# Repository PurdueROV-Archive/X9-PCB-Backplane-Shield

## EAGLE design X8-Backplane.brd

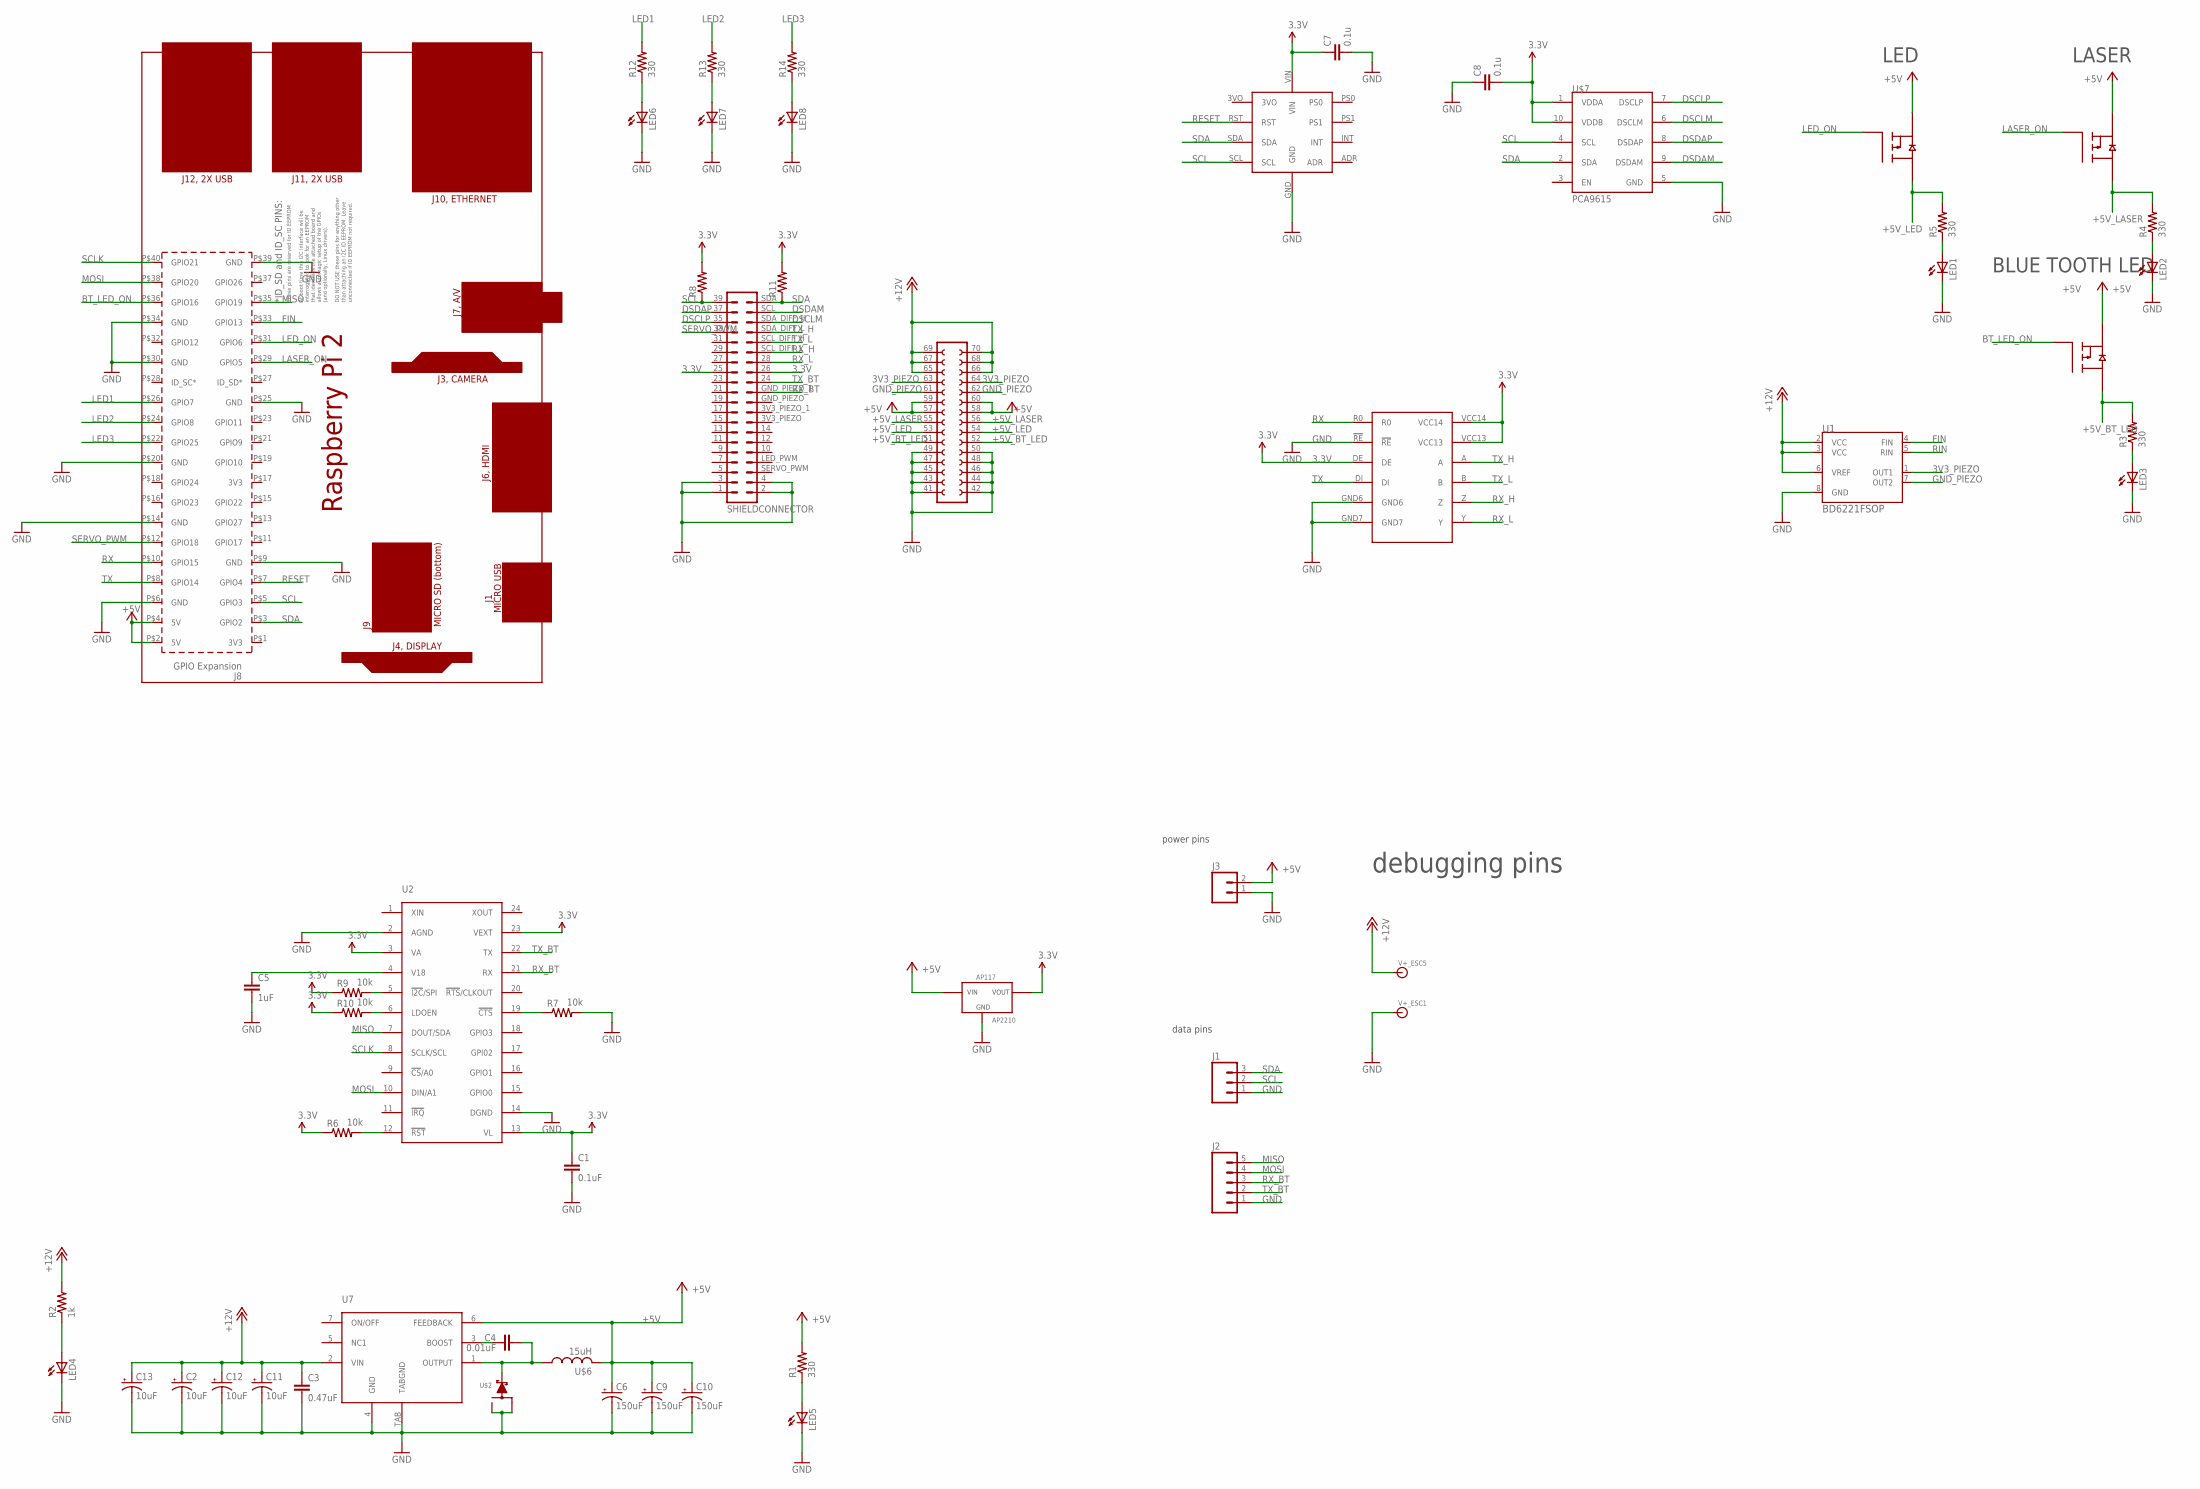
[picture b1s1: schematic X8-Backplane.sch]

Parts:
C1: 0.1uF; 0603-CAP
C2, C11, C12, C13: 10uF; CTAN(7.30_4.30MM)
C3: 0.47uF; 0603
C4: 0.01uF; 0603-CAP
C5: 1uF; 0603-CAP
C6, C9, C10: 150uF; CTAN(7.30_4.30MM)
C7, C8: 0.1u; 0603-CAP
J1: M03PTH; 1X03
J2: M05PTH; 1X05
J3: M02PTH; 1X02
LED1, LED2, LED3, LED4, LED5, LED6, LED7, LED8: LEDSML0603; SML0603
PCB1: RPI2
R1, R3, R4, R5, R12, R13, R14: 330; R0603
R2: 1k; R0603
R6, R7, R9, R10: 10k; 0603-RES
R8, R11: RESISTOR0603-RES; 0603-RES
U1: BD6221FSOP; SOP8
U2: MAX3107SSOP; SSOP-24
U4, U5, U6: FQB27P06; TO263-3
U7: LM2678
U$1: MAX3491
U$2: SWITCHMODE_SCHOTTKY; DPAK-3
U$3: BNO055_9DOF_BREAKOUT; BNO055
U$4: SHIELDCONNECTOR; 20X2PIN
U$5: AP2210; SOT-23-3
U$6: 15uH; HCMA1305
U$7: PCA9615; MSOP_10
V+_ESC1, V+_ESC5: BANANA_CONN

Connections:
3.3V: C1.1, C7.1, C8.2, R6.1, R8.2, R9.1, R10.1, R11.2, U2.3 (VA), U2.13 (VL), U2.23 (VEXT), U$1.DE, U$1.VCC13, U$1.VCC14, U$3.VIN, U$4.25, U$4.26, U$5.VOUT, U$7.1 (VDDA), U$7.10 (VDDB)
3V3_PIEZO: U1.1 (OUT1), U$4.63 (23), U$4.64 (24)
+5V: C6.+, C9.+, C10.+, J3.2, PCB1.P$2 (5V), PCB1.P$4 (5V), R1.2, U4.3 (S2), U5.3 (S2), U6.3 (S2), U7.6 (FEEDBACK), U$4.57 (17), U$4.58 (18), U$4.59 (19), U$4.60 (20), U$5.VIN, U$6.P$2 (2)
+5V_BT_LED: R3.2, U6.TAB (D2), U$4.51 (11), U$4.52 (12)
+5V_LASER: R4.2, U5.TAB (D2), U$4.55 (15), U$4.56 (16)
+5V_LED: R5.2, U4.TAB (D2), U$4.53 (13), U$4.54 (14)
+12V: C2.+, C3.1, C11.+, C12.+, C13.+, R2.2, U1.2 (VCC), U1.3 (VCC), U1.6 (VREF), U7.2 (VIN), U$4.65 (25), U$4.66 (26), U$4.67 (27), U$4.68 (28), U$4.69 (12V), U$4.70 (30), V+_ESC5.P$1
BT_LED_ON: PCB1.P$36 (GPIO16), U6.1 (G2)
DSCLM: U$4.SDA_DIFF_H, U$7.6 (DSCLM)
DSCLP: U$4.35, U$7.7 (DSCLP)
DSDAM: U$4.SCL, U$7.9 (DSDAM)
DSDAP: U$4.37, U$7.8 (DSDAP)
FIN: PCB1.P$33 (GPIO13), U1.4 (FIN)
GND: C1.2, C2.-, C3.2, C5.2, C6.-, C7.2, C8.1, C9.-, C10.-, C11.-, C12.-, C13.-, J1.1, J2.1, J3.1, LED1.C, LED2.C, LED3.C, LED4.C, LED5.C, LED6.C, LED7.C, LED8.C, PCB1.P$6 (GND), PCB1.P$9 (GND), PCB1.P$14 (GND), PCB1.P$20 (GND), PCB1.P$25 (GND), PCB1.P$30 (GND), PCB1.P$34 (GND), PCB1.P$39 (GND), R7.2, U1.8 (GND), U2.2 (AGND), U2.14 (DGND), U7.4 (GND), U7.TAB (TABGND), U$1.!RE, U$1.GND6, U$1.GND7, U$2.P$1, U$2.P$3, U$3.GND, U$4.1, U$4.2, U$4.3, U$4.4, U$4.41 (1), U$4.42 (2), U$4.43 (3), U$4.44 (4), U$4.45 (5), U$4.46 (6), U$4.47 (7), U$4.48 (8), U$4.49 (9), U$4.50 (10), U$5.GND, U$7.5 (GND), V+_ESC1.P$1
GND_PIEZO: U1.7 (OUT2), U$4.61 (21), U$4.62 (22)
LASER_ON: PCB1.P$29 (GPIO5), U5.1 (G2)
LED1: PCB1.P$26 (GPIO7), R12.2
LED2: PCB1.P$24 (GPIO8), R13.2
LED3: PCB1.P$22 (GPIO25), R14.2
LED_ON: PCB1.P$31 (GPIO6), U4.1 (G2)
MISO: J2.5, PCB1.P$35 (GPIO19), U2.7 (DOUT/SDA)
MOSI: J2.4, PCB1.P$38 (GPIO20), U2.10 (DIN/A1)
unnamed: LED5.A, R1.1
unnamed: LED4.A, R2.1
unnamed: LED1.A, R5.1
unnamed: LED2.A, R4.1
unnamed: LED3.A, R3.1
unnamed: R6.2, U2.12 (!RST!)
unnamed: R7.1, U2.19 (!CTS!)
unnamed: C5.1, U2.4 (V18)
unnamed: R9.2, U2.5 (!I2C!/SPI)
unnamed: R10.2, U2.6 (LDOEN)
unnamed: LED6.A, R12.1
unnamed: LED7.A, R13.1
unnamed: LED8.A, R14.1
unnamed: C4.1, U7.3 (BOOST)
unnamed: C4.2, U7.1 (OUTPUT), U$2.P$4, U$6.P$1 (1)
RESET: PCB1.P$7 (GPIO4), U$3.RST
RIN: U1.5 (RIN)
RX: PCB1.P$10 (GPIO15), U$1.R0
RX_BT: J2.3, U2.21 (RX), U$4.GND_PIEZO_1
RX_H: U$1.Z, U$4.SCL_DIFF_L
RX_L: U$1.Y, U$4.28
SCL: J1.2, PCB1.P$5 (GPIO3), R8.1, U$3.SCL, U$4.39, U$7.4 (SCL)
SCLK: PCB1.P$40 (GPIO21), U2.8 (SCLK/SCL)
SDA: J1.3, PCB1.P$3 (GPIO2), R11.1, U$3.SDA, U$4.SDA, U$7.2 (SDA)
SERVO_PWM: PCB1.P$12 (GPIO18), U$4.33
TX: PCB1.P$8 (GPIO14), U$1.DI
TX_BT: J2.2, U2.22 (TX), U$4.24
TX_H: U$1.A, U$4.SDA_DIFF_L
TX_L: U$1.B, U$4.SCL_DIFF_H

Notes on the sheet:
LED
LASER
BLUE TOOTH LED
debugging pins
power pins
data pins

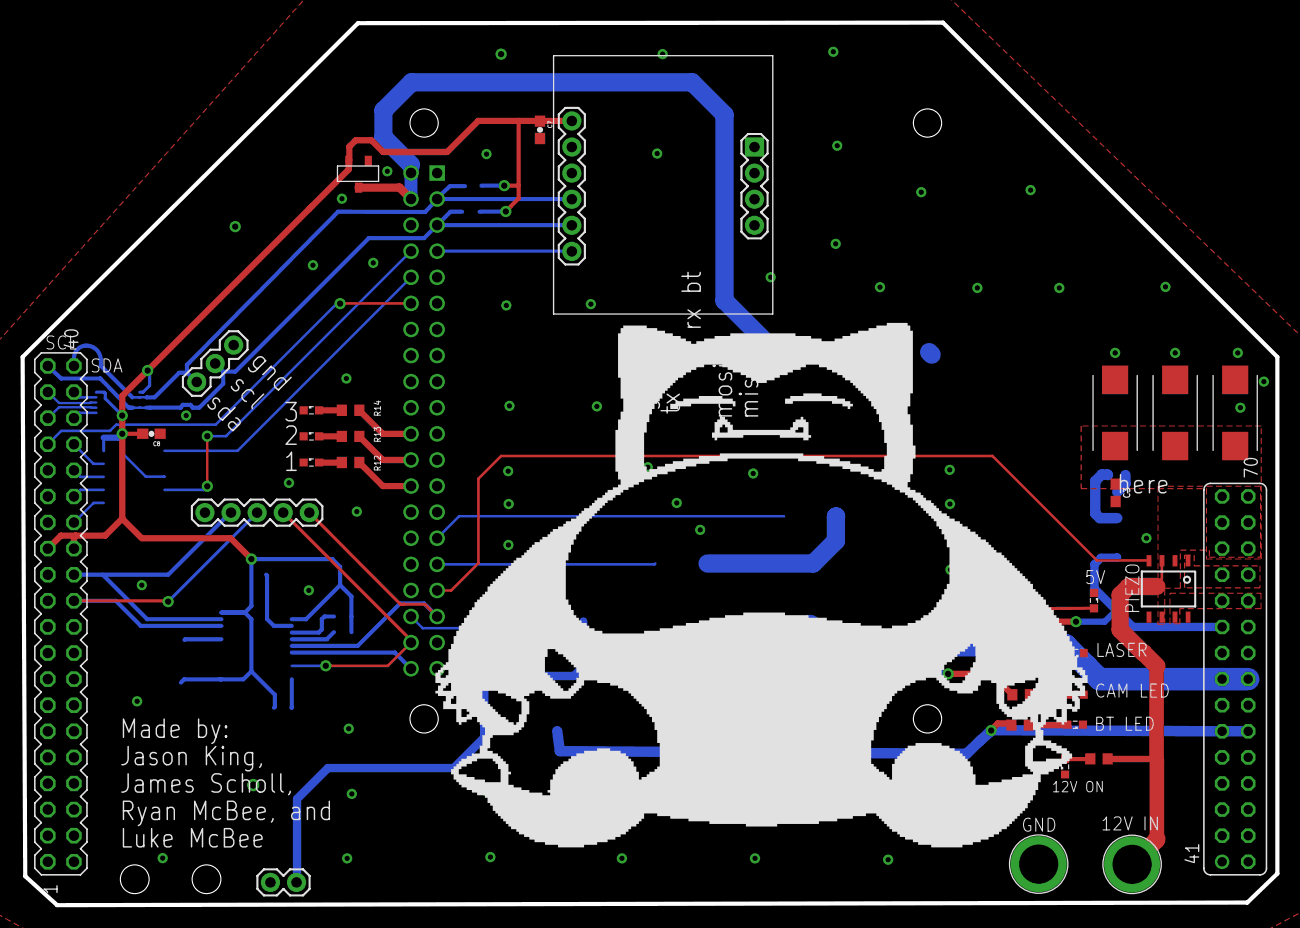
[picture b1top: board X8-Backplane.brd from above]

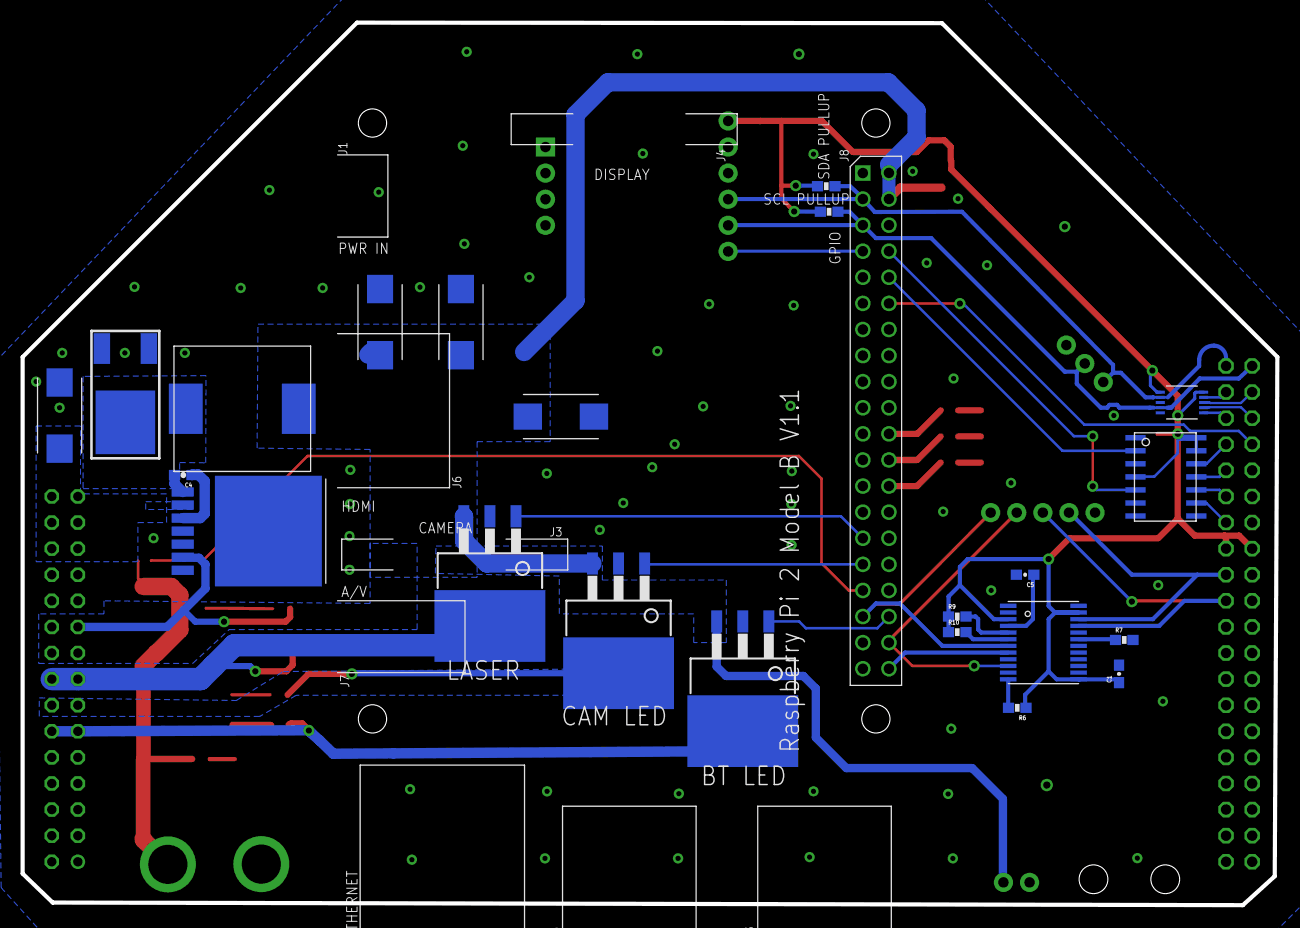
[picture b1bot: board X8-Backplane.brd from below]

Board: 2 copper layers, 122.1 x 85.9 mm, 54 parts (23 on the bottom side), 50 nets.

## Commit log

2016-11-02 OutputJob
2016-11-02 Added part for raspberry pi, 5V -> 3.3V buck converter, and IMU pins
2016-11-03 changed outside perimeter
2016-11-03 small modification to outline
2016-11-05 Intermediate layout
2016-11-05 Finished preliminary layout - probably needs revision
2016-11-06 added brd to brd connector
2016-11-12 because I can
2016-11-16 Mostly routed
2016-11-24 removed buck regulator circuit
2016-11-24 added some new parts
2016-11-24 finished adding components, added descriptions of pins
2016-11-25 first draft of the sechematic. Almost there!
2016-11-25 Added a mosfet for an led for the blue tooth
2016-11-27 Started initial routing on the board
2016-11-27 Leaving the rest to Ryan, not sure I can work with the layout given to me
2016-11-30 Redid routing and moved components
2016-11-30 Moved some more components and added vias to reconnect isolated grounds
2016-12-04 Almost done with routing - stil have to add vias and extra debugging pinouts
2016-12-04 Finished routing except for any debug pins and possible extra vias
2016-12-04 minor changes by Ryan
2016-12-04 made the bottom flat
2016-12-04 added buck regulator
2016-12-04 added more gnd vias
2016-12-07 Moved the buck regulator parts
2016-12-07 To be reviewed
2016-12-07 minor tweaks
2016-12-10 modified wiring of buck regulator
2016-12-10 added LEDs
2016-12-10 added SPI to UART ship
2016-12-11 Wired the spi to serial circuit
2016-12-15 almost done reviewing the board
2016-12-18 add holes for possible usb hub mount
2016-12-19 added two gnd vias
2016-12-21 Fixed routing issues
2016-12-23 modified the silkscreen
2016-12-23 added names
2016-12-24 minor changes to i2c lines
2016-12-26 cleaned up gnd plane and added labels
2016-12-28 added snorlax!
2016-12-29 minor changes
2016-12-30 Edited the silkscreen

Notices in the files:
parts and their libraries:
SparkFun-Passives: Licensing: Creative Commons ShareAlike 4.0 International - https://creativecommons.org/licenses/by-sa/4.0
